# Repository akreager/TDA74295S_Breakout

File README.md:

# TDA7429 Breakout Board & Arduino Library

Breakout board and Arduino library for the ST TDA7429 digitally controlled audio processor with surround sound matrix.

## What is the TDA7429?

The TDA7429 is an I²C-controlled audio DSP designed for TV and Hi-Fi systems. It handles input selection, volume/tone control, surround sound processing, and speaker balance — all through a two-wire serial bus with no external microcontroller overhead beyond simple register writes.

**Key specs:**
- 3 stereo inputs with 0–31.5 dB attenuation (0.5 dB steps)
- Bass, middle, and treble control (±14 dB, 2 dB steps)
- 4 independent speaker attenuators (0–79 dB, 1 dB steps + mute)
- 3 surround modes: music, movie, simulated (256 selectable responses)
- 4 programmable phase shifters
- Monitor and auxiliary outputs
- 106 dB signal-to-noise ratio
- 7–10.2 V supply

## Repository Structure

```
├── pcb/
│   ├── TDA7429_BREAKOUT.kicad_pro      # KiCad project
│   ├── TDA7429_BREAKOUT.kicad_sch      # Schematic
│   ├── TDA7429_BREAKOUT.kicad_pcb      # PCB layout
│   ├── fp-lib-table                    # Footprint library table
│   ├── sym-lib-table                   # Symbol library table
│   ├── eagle2kicad_pcb.py              # Board conversion script
│   ├── eagle2kicad_sch.py              # Schematic conversion script
│   ├── TDA7429_KiCad_Lib/             # Custom KiCad library
│   │   ├── TDA7429.kicad_sym
│   │   └── TDA7429.pretty/
│   │       └── SDIP-42_W15.24mm_P1.778mm.kicad_mod
│   └── Archive Eagle Design/           # Original Eagle 6.5 files
│       ├── TDA7429_BREAKOUT.sch
│       ├── TDA7429_BREAKOUT.brd
│       └── TDA7429_BREAKOUT.pdf
├── TDA7429S TDA7429T.pdf               # Datasheet
├── .gitattributes
├── .gitignore
└── README.md
```

## Hardware

### Breakout Board

~50 × 50 mm board carrying the TDA7429S (SDIP-42) with all external filter components from the datasheet reference circuit. Pin headers break out:

| Header     | Pins                                      |
|------------|-------------------------------------------|
| AUDIO_IN   | 3 stereo input pairs (L/R × IN1–IN3)     |
| AUDIO_OUT  | L_OUT, R_OUT, AUXOUT_L, AUXOUT_R          |
| MONITOR    | MONITOR_L, MONITOR_R                      |
| DATA       | SDA, SCL                                  |
| POWER      | +9V, GND                                  |

### Connecting to Arduino

| Breakout | Arduino Uno/Nano | Arduino Mega |
|----------|------------------|--------------|
| SDA      | A4               | 20           |
| SCL      | A5               | 21           |
| GND      | GND              | GND          |

The TDA7429 runs at 7–10.2 V — do **not** power it from the Arduino 5V pin. Use a separate 9V supply for the breakout board. The I²C bus needs pull-up resistors to the Arduino's 3.3V or 5V (4.7kΩ typical). The chip's I²C thresholds (V_IL max 1V, V_IH min 3V) are compatible with both 3.3V and 5V logic.

## Arduino Library

### Installation

Copy the `firmware/TDA7429/` folder into your Arduino libraries directory, or use the Arduino IDE Library Manager if published.

### Quick Start

```cpp
#include <Wire.h>
#include <TDA7429.h>

TDA7429 audio;

void setup() {
  Wire.begin();
  audio.begin();

  audio.selectInput(1);          // Input 1
  audio.setInputAttenuation(0);  // 0 dB (no attenuation)
  audio.setBass(0);              // Flat
  audio.setMiddle(0);            // Flat
  audio.setTreble(0);            // Flat
  audio.setSpeakerAttenuation(TDA7429_LEFT, -20);   // -20 dB
  audio.setSpeakerAttenuation(TDA7429_RIGHT, -20);  // -20 dB
  audio.setSurroundMode(TDA7429_SURROUND_OFF);
}

void loop() {
  // Adjust volume, tone, etc. from serial commands, buttons, encoder...
}
```

### API Reference

| Method | Description |
|--------|-------------|
| `begin()` | Initialize with default (muted) state |
| `selectInput(1–4)` | Choose stereo input pair |
| `setInputAttenuation(dB)` | 0 to -31.5 dB in 0.5 dB steps |
| `setBass(dB)` | -14 to +14 dB in 2 dB steps |
| `setMiddle(dB)` | -14 to +14 dB in 2 dB steps |
| `setTreble(dB)` | -14 to +14 dB in 2 dB steps |
| `setSpeakerAttenuation(ch, dB)` | 0 to -79 dB per channel, 1 dB steps |
| `setAuxAttenuation(ch, dB)` | 0 to -79 dB per channel, 1 dB steps |
| `setSurroundMode(mode)` | OFF, MUSIC, MOVIE, SIMULATED |
| `setEffectControl(dB)` | -6 to -21 dB surround effect level |
| `setPhaseShifters(...)` | Configure 4 phase shift resistors |
| `mute()` / `unmute()` | Mute/unmute all speaker outputs |

## Known Issues / TODO

- [ ] DIG_GND (pin 28) needs to be connected to ground in the schematic
- [ ] Audio connector ground pins (L-, R-) need explicit connection to AGND
- [ ] Consider adding bottom ground pour for improved noise performance
- [ ] Add ferrite bead between DIG_GND and AGND for digital/analog isolation

## License

Hardware design files are released under [CERN-OHL-P v2](https://ohwr.org/cern_ohl_p_v2.txt). Arduino library is released under the MIT License. See individual directories for details.

## Credits

Board design by Allen Kreager. Originally designed in Eagle 6.5, converted to KiCad 7.

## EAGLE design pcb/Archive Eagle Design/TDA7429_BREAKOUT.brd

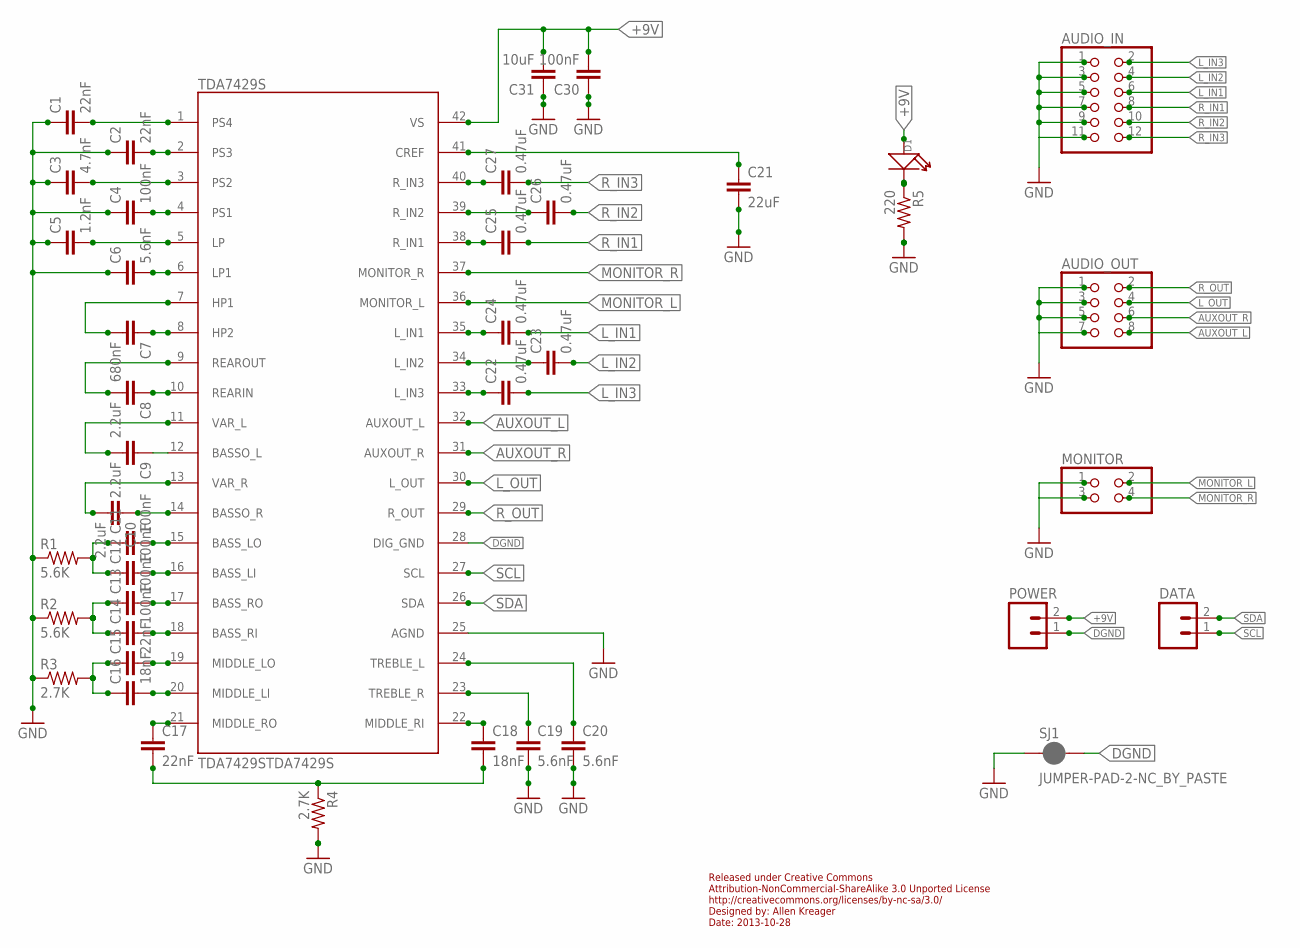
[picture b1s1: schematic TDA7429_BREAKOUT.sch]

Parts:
AUDIO_IN: PINHD-2X6; 2X06
AUDIO_OUT: PINHD-2X4; 2X04
C1, C2, C15, C17: 22nF; 0805
C3: 4.7nF; 0805
C4, C11, C12, C13, C14, C30: 100nF; 0805
C5: 1.2nF; 0805
C6, C19, C20: 5.6nF; 0805
C7: 680nF; 0805
C8, C9, C10: 2.2uF; 0805
C16, C18: 18nF; 0805
C21: 22uF; 0805
C22, C23, C24, C25, C26, C27: 0.47uF; 0805
C31: 10uF; 0805
D1: LED; LED0603
DATA: M02PTH; 1X02
MONITOR: PINHD-2X2; 2X02
POWER: M02PTH; 1X02
R1, R2: 5.6K; 0805
R3, R4: 2.7K; 0805
R5: 220; 0805
SJ1: JUMPER-PAD-2-NC_BY_PASTE; PAD-JUMPER-2-NC_BY_PASTE_YES_SILK
TDA7429S: TDA7429STDA7429S; SDIP42

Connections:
+9V: C30.2, C31.2, D1.+, POWER.2, TDA7429S.42 (VS)
AUXOUT_L: AUDIO_OUT.8, TDA7429S.32 (AUXOUT_L)
AUXOUT_R: AUDIO_OUT.6, TDA7429S.31 (AUXOUT_R)
DGND: POWER.1, SJ1.2, TDA7429S.28 (DIG_GND)
GND: AUDIO_IN.1, AUDIO_IN.3, AUDIO_IN.5, AUDIO_IN.7, AUDIO_IN.9, AUDIO_IN.11, AUDIO_OUT.1, AUDIO_OUT.3, AUDIO_OUT.5, AUDIO_OUT.7, C1.1, C2.1, C3.1, C4.1, C5.1, C6.1, C19.2, C20.2, C21.2, C30.1, C31.1, MONITOR.1, MONITOR.3, R1.1, R2.1, R3.1, R4.2, R5.2, SJ1.1, TDA7429S.25 (AGND)
HP1: C7.2, TDA7429S.7 (HP1)
L_IN1: AUDIO_IN.6, C24.2
L_IN2: AUDIO_IN.4, C23.2
L_IN3: AUDIO_IN.2, C22.2
L_OUT: AUDIO_OUT.4, TDA7429S.30 (L_OUT)
MONITOR_L: MONITOR.2, TDA7429S.36 (MONITOR_L)
MONITOR_R: MONITOR.4, TDA7429S.37 (MONITOR_R)
unnamed: D1.-, R5.1
unnamed: C9.1, TDA7429S.12 (BASSO_L)
unnamed: C3.2, TDA7429S.3 (PS2)
unnamed: C1.2, TDA7429S.1 (PS4)
unnamed: C2.2, TDA7429S.2 (PS3)
unnamed: C4.2, TDA7429S.4 (PS1)
unnamed: C5.2, TDA7429S.5 (LP)
unnamed: C6.2, TDA7429S.6 (LP1)
unnamed: C7.1, TDA7429S.8 (HP2)
unnamed: C8.1, TDA7429S.10 (REARIN)
unnamed: C10.1, TDA7429S.14 (BASSO_R)
unnamed: C11.2, TDA7429S.15 (BASS_LO)
unnamed: C11.1, C12.1, R1.2
unnamed: C12.2, TDA7429S.16 (BASS_LI)
unnamed: C13.2, TDA7429S.17 (BASS_RO)
unnamed: C13.1, C14.1, R2.2
unnamed: C14.2, TDA7429S.18 (BASS_RI)
unnamed: C15.2, TDA7429S.19 (MIDDLE_LO)
unnamed: C16.2, TDA7429S.20 (MIDDLE_LI)
unnamed: C15.1, C16.1, R3.2
unnamed: C17.1, TDA7429S.21 (MIDDLE_RO)
unnamed: C18.1, TDA7429S.22 (MIDDLE_RI)
unnamed: C17.2, C18.2, R4.1
unnamed: C19.1, TDA7429S.23 (TREBLE_R)
unnamed: C20.1, TDA7429S.24 (TREBLE_L)
unnamed: C27.1, TDA7429S.40 (R_IN3)
unnamed: C26.1, TDA7429S.39 (R_IN2)
unnamed: C25.1, TDA7429S.38 (R_IN1)
unnamed: C24.1, TDA7429S.35 (L_IN1)
unnamed: C23.1, TDA7429S.34 (L_IN2)
unnamed: C22.1, TDA7429S.33 (L_IN3)
unnamed: C21.1, TDA7429S.41 (CREF)
REAROUT: C8.2, TDA7429S.9 (REAROUT)
R_IN1: AUDIO_IN.8, C25.2
R_IN2: AUDIO_IN.10, C26.2
R_IN3: AUDIO_IN.12, C27.2
R_OUT: AUDIO_OUT.2, TDA7429S.29 (R_OUT)
SCL: DATA.1, TDA7429S.27 (SCL)
SDA: DATA.2, TDA7429S.26 (SDA)
VAR_L: C9.2, TDA7429S.11 (VAR_L)
VAR_R: C10.2, TDA7429S.13 (VAR_R)

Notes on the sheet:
Released under Creative Commons Attribution-NonCommercial-ShareAlike 3.0 Unported License http://creativecommons.org/licenses/by-nc-sa/3.0/ Designed by: Allen Kreager Date: 2013-10-28

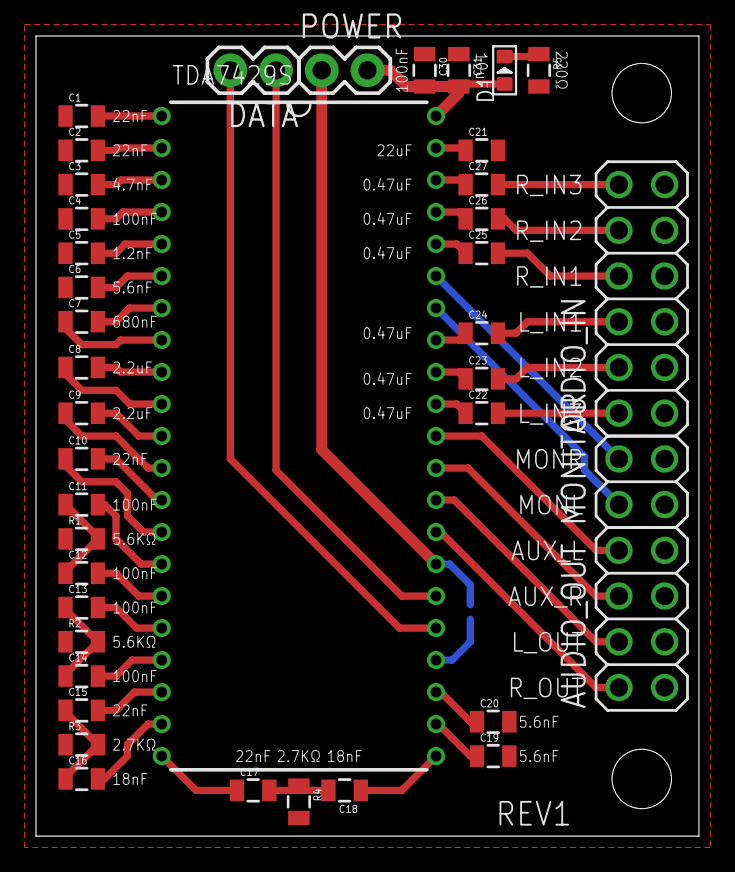
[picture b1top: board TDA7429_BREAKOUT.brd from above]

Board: 2 copper layers, 36.8 x 44.5 mm, 44 parts (1 on the bottom side), 53 nets.

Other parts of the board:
U$1, U$2: STAND-OFF

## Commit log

2015-08-07 :circus_tent: Added .gitattributes & .gitignore files
2015-08-07 TDA7429 audio DSP IC breakout board
2015-08-08 TDA7429 datasheet
2026-03-07 revive project and prepare for migration to kicad design and arduino library
2026-03-07 add readme
2026-03-07 inital kicad conversion
2026-03-07 Update project directory structure
2026-03-07 Add symbol that matches datasheet test circuit.
2026-03-07 start redesigning schematic
2026-03-08 update schematic
2026-03-08 tweak schematic, add i2c pullup resistors.
2026-03-09 add reference docs

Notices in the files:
parts and their libraries:
SparkFun-Connectors: Licensing: CC v3.0 Share-Alike You are welcome to use this library for commercial purposes.
SparkFun-Aesthetics: Licensing: Creative Commons ShareAlike 4.0 International - https://creativecommons.org/licenses/by-sa/4.0
